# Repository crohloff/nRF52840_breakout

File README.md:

# nRF52840_breakout

## Low Cost variant
The low cost variant has four layers but no micro vias, no sensors and different components for the power circuit

## Tool used

 - KiCad 5.0.2

## Custom symbols

 - Custom symbols are placed inside the folder custom_symbols
 - Added as Project Specific Libraries

## Custom footprints

 - Custom footprints are placed inside the folder custom_footprints
 - Added as Project Specific Libraries

## Todo

 -

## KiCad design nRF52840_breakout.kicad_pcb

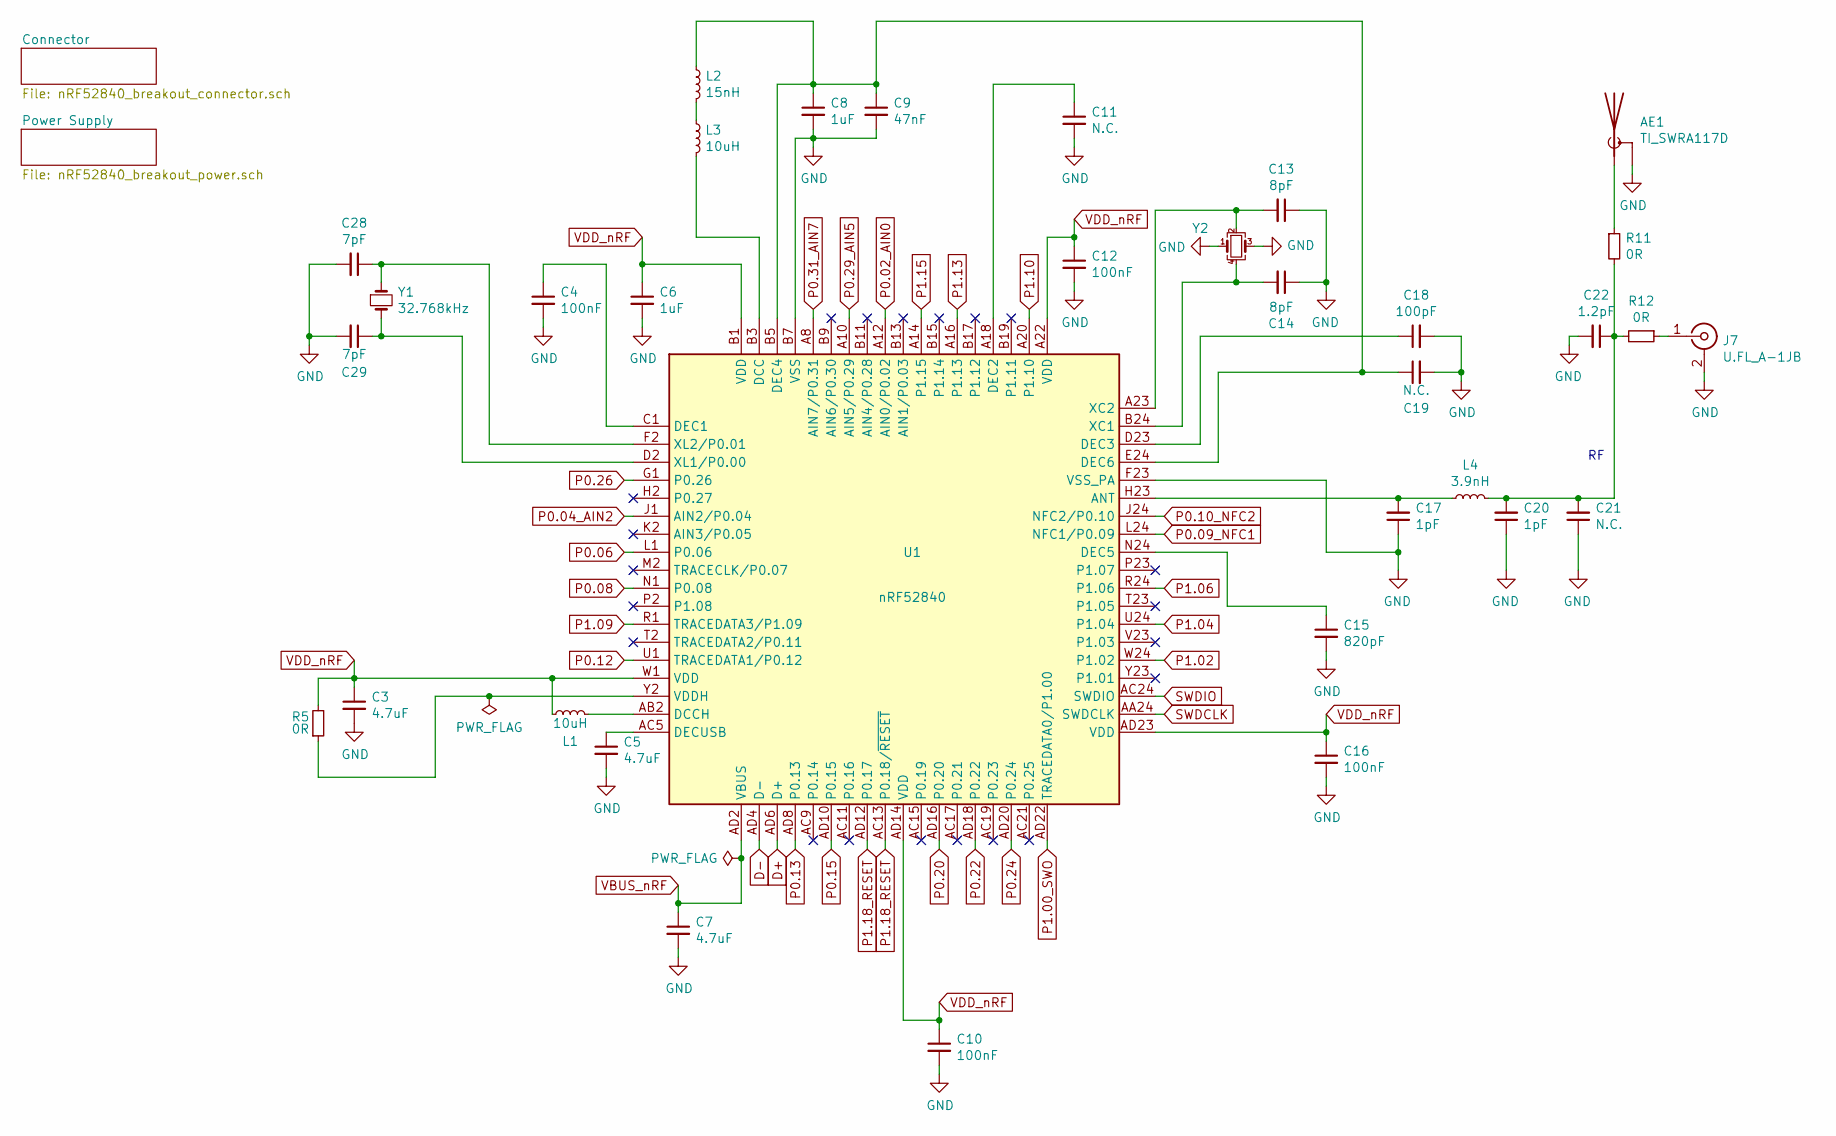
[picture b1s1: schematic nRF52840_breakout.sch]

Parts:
AE1: TI_SWRA117D; Texas_SWRA117D_2.4GHz_Right
C3, C5, C7: 4.7uF; C_0402_1005Metric; MFG P/N JMK105BBJ475MV-F; Digikey 587-2787-1-ND
C4, C10, C12, C16: 100nF; C_0402_1005Metric; MFG P/N CL05A104KP5NNNC; Digikey 1276-1022-1-ND
C6, C8: 1uF; C_0402_1005Metric; MFG P/N CL05A105KO5NNNC; Digikey 1276-1067-1-ND
C9: 47nF; C_0402_1005Metric; MFG P/N CC0402KRX7R9BB473; Digikey 311-3815-1-ND
C11, C19, C21: N.C.; C_0402_1005Metric
C13, C14: 8pF; C_0402_1005Metric; MFG P/N CC0402CRNPO9BN8R0; Digikey 311-3328-1-ND
C15: 820pF; C_0402_1005Metric; MFG P/N CL05B821KB5NNNC; Digikey 1276-1589-1-ND
C17, C20: 1pF; C_0402_1005Metric; MFG P/N CC0402CRNPO9BN1R0; Digikey 311-2076-1-ND
C18: 100pF; C_0402_1005Metric; MFG P/N CC0402JRNPO9BN101; Digikey 311-1024-1-ND
C22: 1.2pF; C_0402_1005Metric; MFG P/N CC0402CRNPO9BN1R2; Digikey 311-1002-1-ND
C28, C29: 7pF; C_0402_1005Metric; MFG P/N GRM1555C1H7R0BA01D; Digikey 490-6254-1-ND
J7: U.FL_A-1JB; CON_AMP_A-1JB; MFG P/N A-1JB; Digikey ARF1579CT-ND
L1, L3: 10uH; L_0603_1608Metric; MFG P/N LQM18FN100M00D; Digikey 490-4025-1-ND
L2: 15nH; L_0402_1005Metric; MFG P/N LQW15AN15NG00D; Digikey 490-6771-1-ND
L4: 3.9nH; L_0402_1005Metric; MFG P/N LQG15HN3N9S02D; Digikey 490-1079-1-ND
R5, R11, R12: 0R; R_0402_1005Metric; MFG P/N RC0402JR-070RL; Digikey 311-0.0JRCT-ND
U1: nRF52840; Nordic_AQFN-73-1EP_7x7mm_P0.5mm; MFG P/N NRF52840-QIAA-R; Digikey 1490-1071-1-ND
Y1: 32.768kHz; Crystal_SMD_2012-2Pin_2.0x1.2mm; MFG P/N SC20S-7PF20PPM; Digikey 728-1076-1-ND
Y2: 32MHz; Crystal_SMD_2016-4Pin_2.0x1.6mm; MFG P/N X201632MKD4SI; LCSC C108165

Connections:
D+: U1.AD6 (D+); also elsewhere on the board
D-: U1.AD4 (D-); also elsewhere on the board
unnamed: AE1.1 (A), R11.1
unnamed: C4.1, U1.C1 (DEC1)
unnamed: C5.1, U1.AC5 (DECUSB)
unnamed: C11.1, U1.A18 (DEC2)
unnamed: C15.1, U1.N24 (DEC5)
unnamed: C17.2, L4.2, U1.H23 (ANT)
unnamed: C18.1, U1.D23 (DEC3)
unnamed: C8.1, C9.1, C19.1, L2.1, U1.B5 (DEC4), U1.E24 (DEC6)
unnamed: C20.2, C21.2, C22.1, L4.1, R11.2, R12.2
unnamed: C28.1, U1.F2 (XL2/P0.01), Y1.1
unnamed: C29.1, U1.D2 (XL1/P0.00), Y1.2
unnamed: J7.1 (In), R12.1
unnamed: L1.2, U1.AB2 (DCCH)
unnamed: L2.2, L3.1
unnamed: L3.2, U1.B3 (DCC)
unnamed: R5.1, U1.Y2 (VDDH)
P0.02_AIN0: U1.A12 (AIN0/P0.02); also elsewhere on the board
P0.04_AIN2: U1.J1 (AIN2/P0.04); also elsewhere on the board
P0.06: U1.L1 (P0.06); also elsewhere on the board
P0.08: U1.N1 (P0.08); also elsewhere on the board
P0.09_NFC1: U1.L24 (NFC1/P0.09); also elsewhere on the board
P0.10_NFC2: U1.J24 (NFC2/P0.10); also elsewhere on the board
P0.12: U1.U1 (TRACEDATA1/P0.12); also elsewhere on the board
P0.13: U1.AD8 (P0.13); also elsewhere on the board
P0.15: U1.AD10 (P0.15); also elsewhere on the board
P0.20: U1.AD16 (P0.20); also elsewhere on the board
P0.22: U1.AD18 (P0.22); also elsewhere on the board
P0.24: U1.AD20 (P0.24); also elsewhere on the board
P0.26: U1.G1 (P0.26); also elsewhere on the board
P0.29_AIN5: U1.A10 (AIN5/P0.29); also elsewhere on the board
P0.31_AIN7: U1.A8 (AIN7/P0.31); also elsewhere on the board
P1.00_SWO: U1.AD22 (TRACEDATA0/P1.00); also elsewhere on the board
P1.02: U1.W24 (P1.02); also elsewhere on the board
P1.04: U1.U24 (P1.04); also elsewhere on the board
P1.06: U1.R24 (P1.06); also elsewhere on the board
P1.09: U1.R1 (TRACEDATA3/P1.09); also elsewhere on the board
P1.10: U1.A20 (P1.10); also elsewhere on the board
P1.13: U1.A16 (P1.13); also elsewhere on the board
P1.15: U1.A14 (P1.15); also elsewhere on the board
P1.18_RESET: U1.AC13 (P0.18/~RESET), U1.AD12 (P0.17); also elsewhere on the board
SWDCLK: U1.AA24 (SWDCLK); also elsewhere on the board
SWDIO: U1.AC24 (SWDIO); also elsewhere on the board
VBUS_nRF: C7.1, U1.AD2 (VBUS); also elsewhere on the board
VDD_nRF: C3.1, C6.1, C10.1, C12.1, C16.1, L1.1, R5.2, U1.A22 (VDD), U1.AD14 (VDD), U1.AD23 (VDD), U1.B1 (VDD), U1.W1 (VDD); also elsewhere on the board

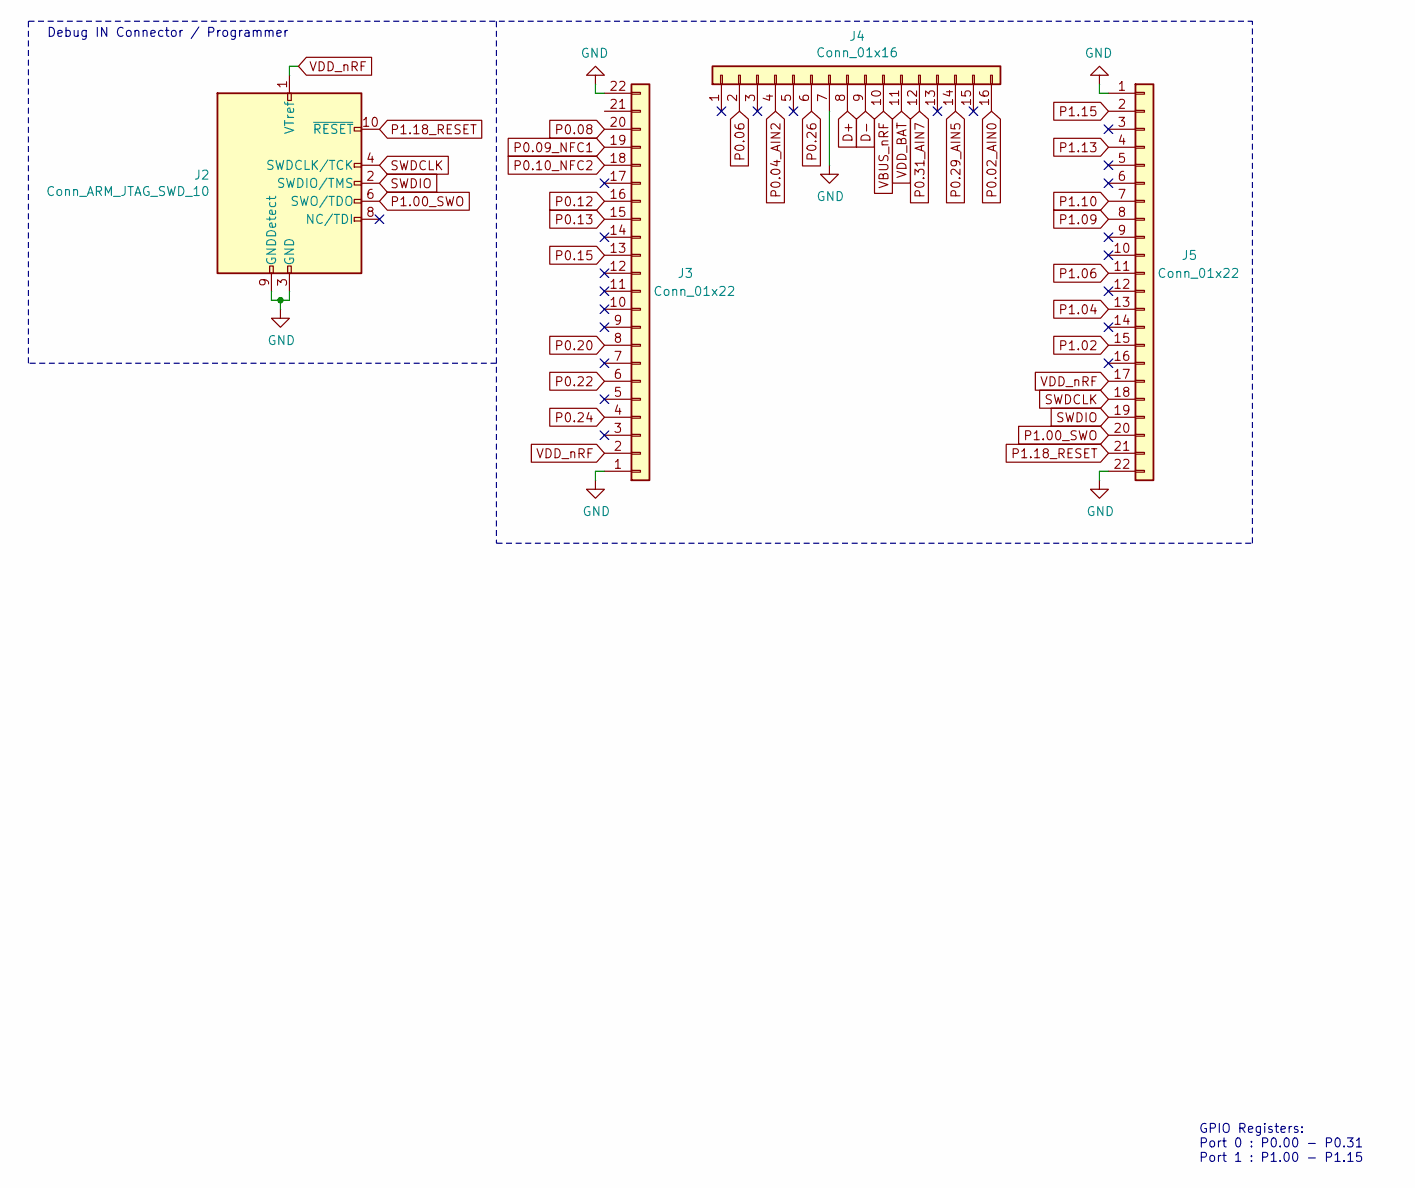
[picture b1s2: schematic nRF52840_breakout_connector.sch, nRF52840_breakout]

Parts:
J2: Conn_ARM_JTAG_SWD_10; PinHeader_2x05_P1.27mm_Vertical_SMD; MFG P/N 20021121-00010C4LF; Digikey 609-3695-1-ND
J3, J5: Conn_01x22; PinHeader_1x22_P1.27mm_Vertical
J4: Conn_01x16; PinHeader_1x16_P1.27mm_Vertical

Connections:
D+: J4.8; also elsewhere on the board
D-: J4.9; also elsewhere on the board
P0.02_AIN0: J4.16; also elsewhere on the board
P0.04_AIN2: J4.4; also elsewhere on the board
P0.06: J4.2; also elsewhere on the board
P0.08: J3.20; also elsewhere on the board
P0.09_NFC1: J3.19; also elsewhere on the board
P0.10_NFC2: J3.18; also elsewhere on the board
P0.12: J3.16; also elsewhere on the board
P0.13: J3.15; also elsewhere on the board
P0.15: J3.13; also elsewhere on the board
P0.20: J3.8; also elsewhere on the board
P0.22: J3.6; also elsewhere on the board
P0.24: J3.4; also elsewhere on the board
P0.26: J4.6; also elsewhere on the board
P0.29_AIN5: J4.14; also elsewhere on the board
P0.31_AIN7: J4.12; also elsewhere on the board
P1.00_SWO: J2.6 (SWO/TDO), J5.20; also elsewhere on the board
P1.02: J5.15; also elsewhere on the board
P1.04: J5.13; also elsewhere on the board
P1.06: J5.11; also elsewhere on the board
P1.09: J5.8; also elsewhere on the board
P1.10: J5.7; also elsewhere on the board
P1.13: J5.4; also elsewhere on the board
P1.15: J5.2; also elsewhere on the board
P1.18_RESET: J2.10 (~RESET~), J5.21; also elsewhere on the board
SWDCLK: J2.4 (SWDCLK/TCK), J5.18; also elsewhere on the board
SWDIO: J2.2 (SWDIO/TMS), J5.19; also elsewhere on the board
VBUS_nRF: J4.10; also elsewhere on the board
VDD_BAT: J4.11; also elsewhere on the board
VDD_nRF: J2.1 (VTref), J3.2, J5.17; also elsewhere on the board

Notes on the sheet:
Debug IN Connector / Programmer
GPIO Registers: Port 0 : P0.00 - P0.31 Port 1 : P1.00 - P1.15

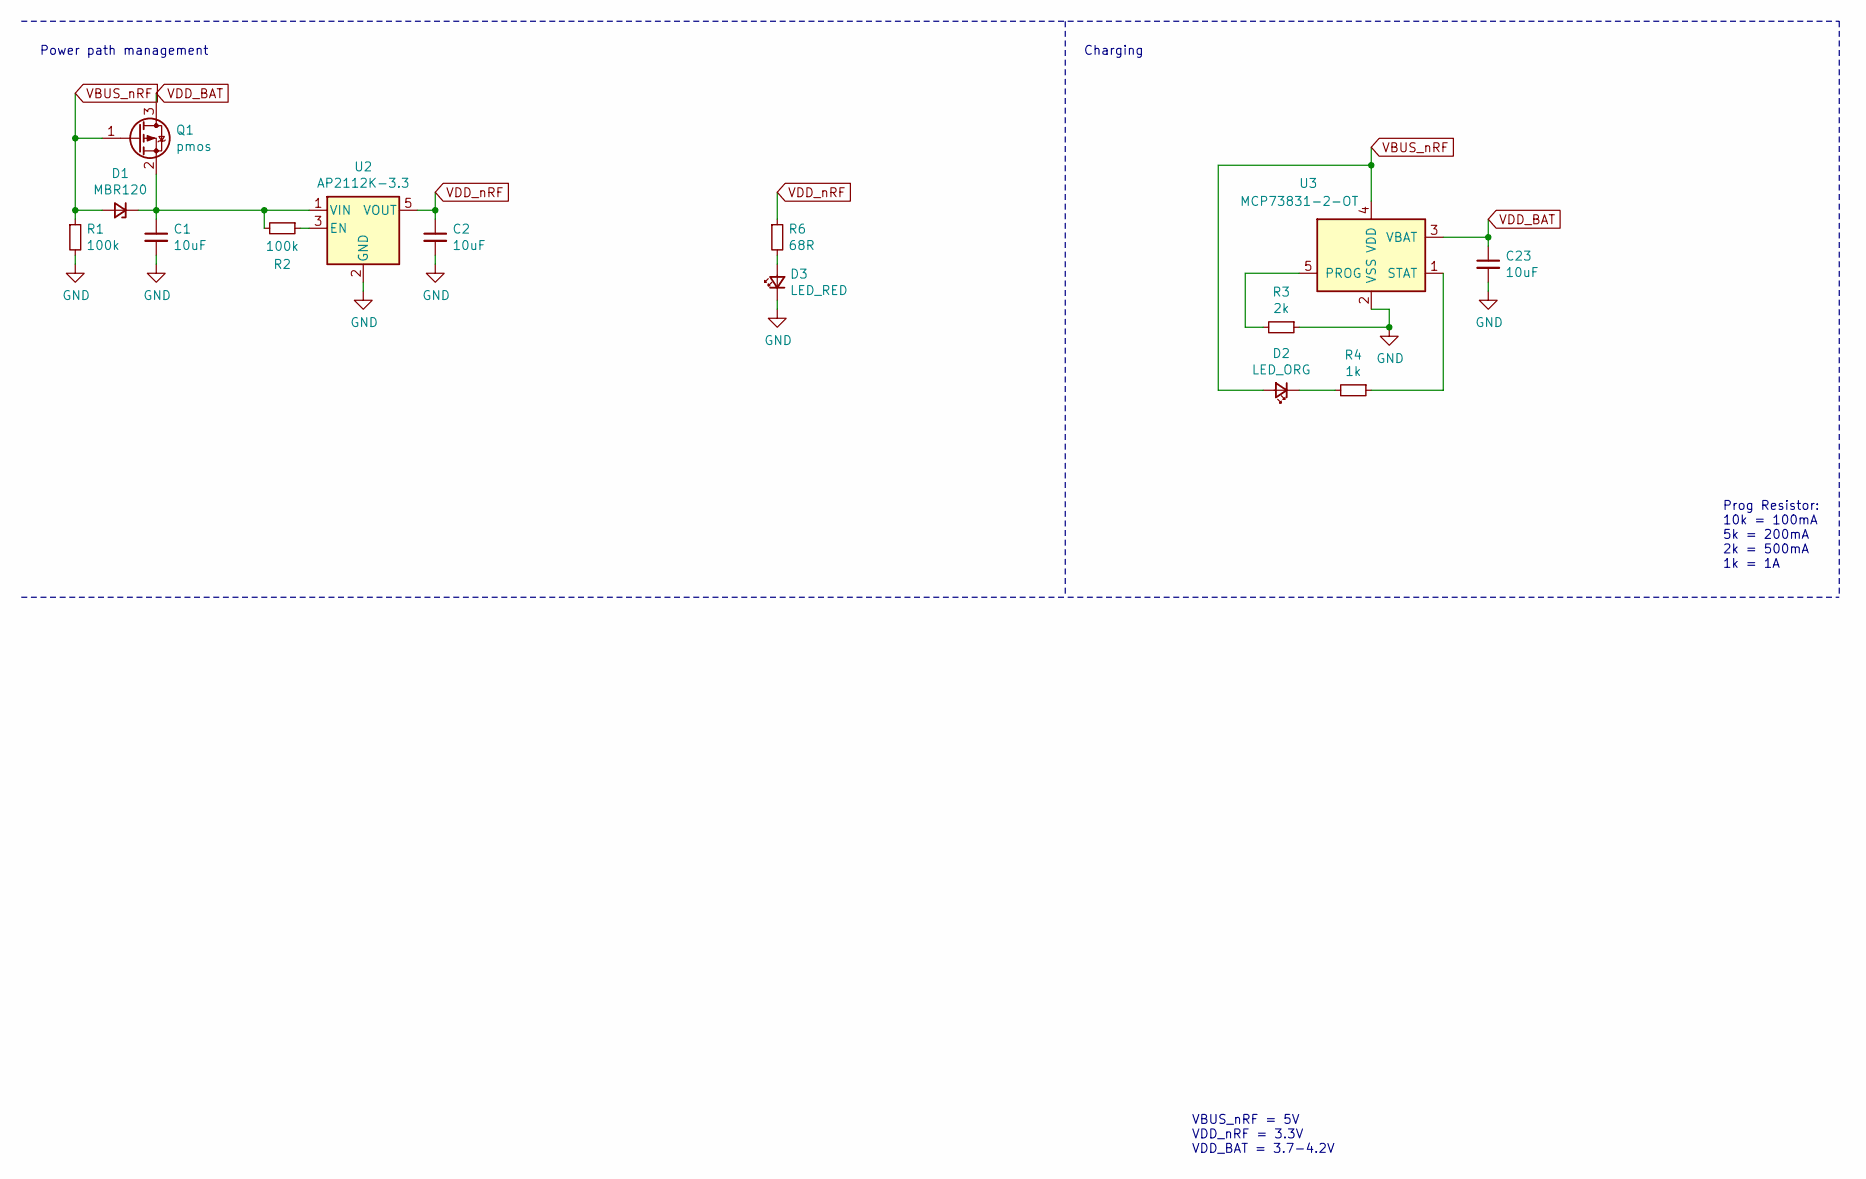
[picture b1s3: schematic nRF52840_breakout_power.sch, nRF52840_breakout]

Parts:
C1, C2, C23: 10uF; C_0402_1005Metric; MFG P/N CL05A106MQ5NUNC; Digikey 1276-1451-1-ND
D1: MBR120; D_SOD-123; MFG P/N MBR120VLSFT1G; Digikey MBR120VLSFT1GOSCT-ND
D2: LED_ORG; LED_0603_1608Metric; MFG P/N LTST-C190KFKT; Digikey 160-1434-1-ND
D3: LED_RED; LED_0603_1608Metric; MFG P/N LTST-C191KRKT; Digikey 160-1447-1-ND
Q1: pmos; SOT-23; MFG P/N NTR1P02T1G; Digikey NTR1P02T1GOSTR-ND
R1, R2: 100k; R_0402_1005Metric; MFG P/N RC0402JR-07100KL; Digikey 311-100KJRCT-ND
R3: 2k; R_0402_1005Metric; MFG P/N RC0402FR-072KL; Digikey 311-2KLRCT-ND
R4: 1k; R_0402_1005Metric; MFG P/N RC0402JR-071KL; Digikey 311-1.0KJRCT-ND
R6: 68R; R_0402_1005Metric; MFG P/N AC0402FR-0768RL; Digikey YAG3507CT-ND
U2: AP2112K-3.3; SOT-23-5; MFG P/N AP2112K-3.3TRG1; Digikey AP2112K-3.3TRG1DICT-ND
U3: MCP73831-2-OT; SOT-23-5; MFG P/N MCP73831T-2ATI/OT; Digikey MCP73831T-2ATI/OTCT-ND

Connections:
unnamed: C1.1, D1.1 (K), Q1.2 (S), R2.2, U2.1 (VIN)
unnamed: D2.1 (K), R4.2
unnamed: D3.2 (A), R6.2
unnamed: R2.1, U2.3 (EN)
unnamed: R3.2, U3.5 (PROG)
unnamed: R4.1, U3.1 (STAT)
VBUS_nRF: D1.2 (A), D2.2 (A), Q1.1 (G), R1.1, U3.4 (VDD); also elsewhere on the board
VDD_BAT: C23.1, Q1.3 (D), U3.3 (VBAT); also elsewhere on the board
VDD_nRF: C2.1, R6.1, U2.5 (VOUT); also elsewhere on the board

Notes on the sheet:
VBUS_nRF = 5V VDD_nRF = 3.3V VDD_BAT = 3.7-4.2V
Power path management
Prog Resistor: 10k = 100mA 5k = 200mA 2k = 500mA 1k = 1A
Charging

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
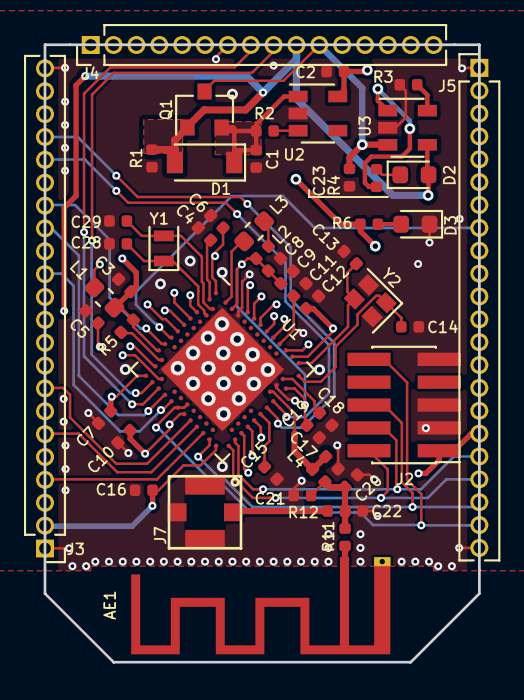
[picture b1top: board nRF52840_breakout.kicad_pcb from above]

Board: 4 copper layers, 24.1 x 34.3 mm, 52 parts (0 on the bottom side), 56 nets.

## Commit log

2019-03-22 added custom antenna footprints
2019-03-22 custom footprint for coax connector with switch
2019-03-24 usb-c custom footprint and 3d model
2019-03-24 changed crystal load capacitance according to component / minor changes
2019-03-24 switched nfc antenna connector
2019-03-26 switched battery connector
2019-03-26 minor changes to schematic and layout
2019-04-18 added som like version of the breakout
2019-04-25 path selection/charging/bme680 sensor integration
2019-05-02 add u.fl conn footprint
2019-05-02 add SiT1533 footprint
2019-05-02 add rgb led footprint and symbol
2019-05-02 minor changes / switched from tag - 10pol debug connector
2019-05-02 changed pin 3/11 to passive
2019-05-02 layout / added part details etc
2019-07-21 2 layer som version
2019-07-21 different power path management / got rid of var components
2019-07-23 modified bom / fixed silk,fab / added 3D models
2019-07-23 clean up
2019-07-23 clean up silk, fab
2019-07-23 minor changes
2019-09-24 fixed crystal y2 90deg turn
2019-09-24 readme
2019-11-10 fixed unrouted vdd with castellated holes
2019-11-17 add LICENSE
2019-11-26 gitignore
2020-01-14 added keepout and edited edge cuts
2020-10-20 add missing gnd to charge ic
